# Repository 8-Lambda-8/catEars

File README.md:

# A CatEar headband with LEDs!

[Interactive BOM](https://htmlpreview.github.io/?https://raw.githubusercontent.com/8-Lambda-8/catEars/master/bom/ibom.html)

## Some components are only needed on one of each Pair of ears:
* U1 - ESP01
* U2 - AMS1117-3.3 (3.3V voltage regulator for the ESP)
* C11, C12 - 22uF (Capacitors for voltage regualtor)
* R1, R2, R3 - 10kΩ Resistors (Pull up/donw Resistors for booting the ESP)
* R4 - 120Ω Resistor (signal output from ESP to th WS2812) 

(3D print the CatEars with transparent materials)

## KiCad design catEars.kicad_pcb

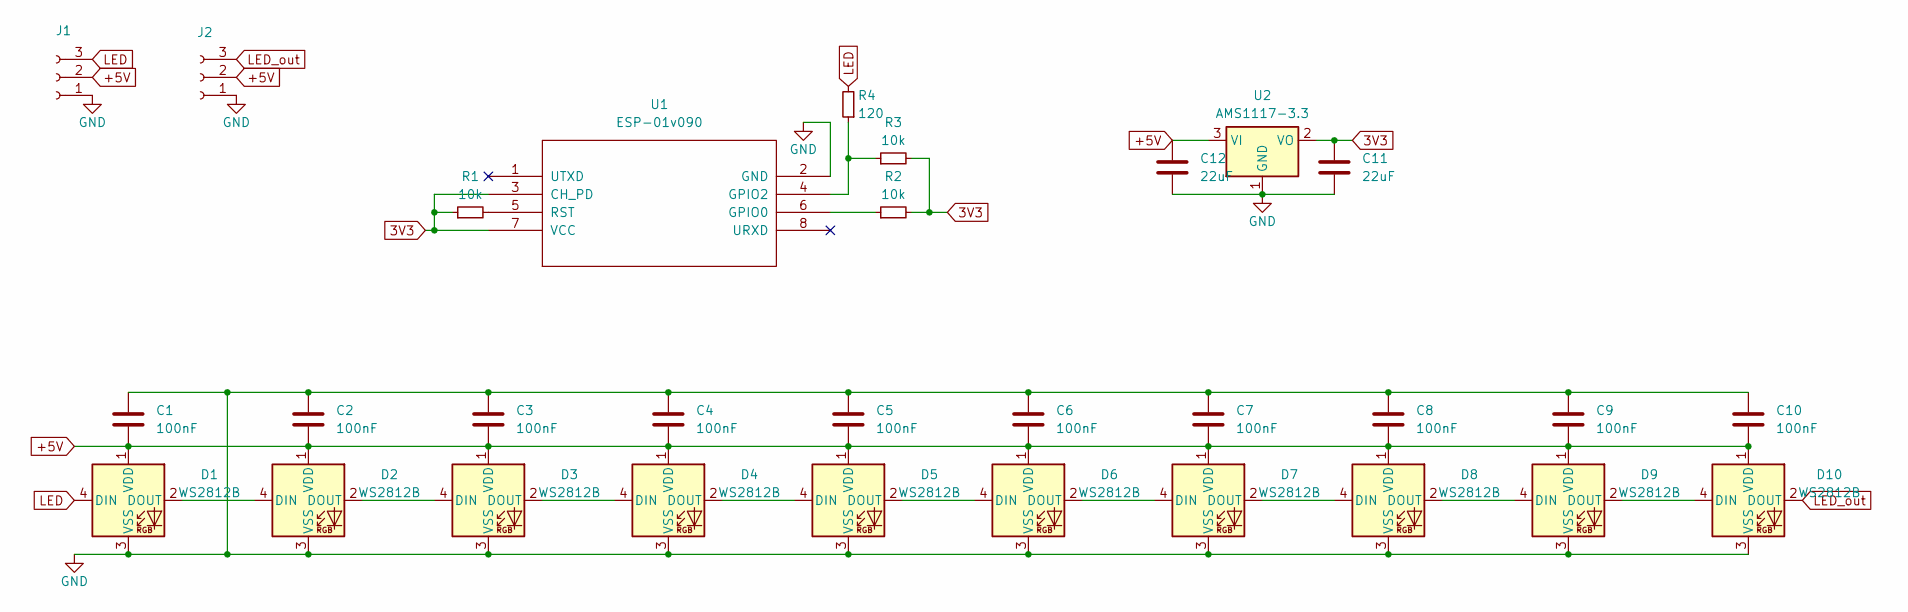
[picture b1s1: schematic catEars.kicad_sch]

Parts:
C1, C2, C3, C4, C5, C6, C7, C8, C9, C10: 100nF; C_0805_2012Metric_Pad1.18x1.45mm_HandSolder
C11, C12: 22uF; C_0805_2012Metric_Pad1.18x1.45mm_HandSolder
D1, D2, D3, D4, D5, D6, D7, D8, D9, D10: WS2812B; LED_WS2812B_PLCC4_5.0x5.0mm_P3.2mm
J1, J2: PinHeader_1x03_P2.54mm_Vertical
R1, R2, R3: 10k; R_0805_2012Metric_Pad1.20x1.40mm_HandSolder
R4: 120; R_0805_2012Metric_Pad1.20x1.40mm_HandSolder
U1: ESP-01v090; ESP-01
U2: AMS1117-3.3; SOT-223-3_TabPin2

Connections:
3V3: C11.1, R1.1, R2.2, R3.2, U1.3 (CH_PD), U1.7 (VCC), U2.2 (VO); also elsewhere on the board
+5V: C1.2, C2.2, C3.2, C4.2, C5.2, C6.2, C7.2, C8.2, C9.2, C10.2, C12.1, D1.1 (VDD), D2.1 (VDD), D3.1 (VDD), D4.1 (VDD), D5.1 (VDD), D6.1 (VDD), D7.1 (VDD), D8.1 (VDD), D9.1 (VDD), D10.1 (VDD), J1.2, J2.2, U2.3 (VI)
GND: C1.1, C2.1, C3.1, C4.1, C5.1, C6.1, C7.1, C8.1, C9.1, C10.1, C11.2, C12.2, D1.3 (VSS), D2.3 (VSS), D3.3 (VSS), D4.3 (VSS), D5.3 (VSS), D6.3 (VSS), D7.3 (VSS), D8.3 (VSS), D9.3 (VSS), D10.3 (VSS), J1.1, J2.1, U1.2 (GND), U2.1 (GND); also elsewhere on the board
LED: D1.4 (DIN), J1.3, R4.2
LED_out: D10.2 (DOUT), J2.3
unnamed: D1.2 (DOUT), D2.4 (DIN)
unnamed: D2.2 (DOUT), D3.4 (DIN)
unnamed: D3.2 (DOUT), D4.4 (DIN)
unnamed: D4.2 (DOUT), D5.4 (DIN)
unnamed: D5.2 (DOUT), D6.4 (DIN)
unnamed: D6.2 (DOUT), D7.4 (DIN)
unnamed: D7.2 (DOUT), D8.4 (DIN)
unnamed: D8.2 (DOUT), D9.4 (DIN)
unnamed: D9.2 (DOUT), D10.4 (DIN)
unnamed 14: R2.1, U1.6 (GPIO0); also elsewhere on the board
unnamed 15: R3.1, R4.1, U1.4 (GPIO2); also elsewhere on the board
unnamed 16: R1.2, U1.5 (RST); also elsewhere on the board

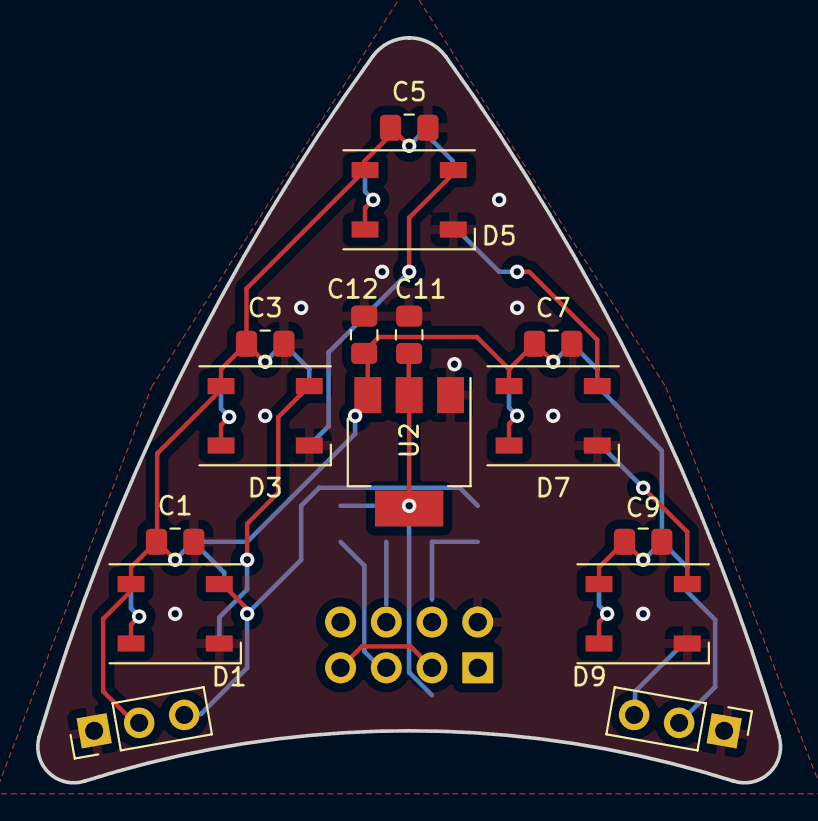
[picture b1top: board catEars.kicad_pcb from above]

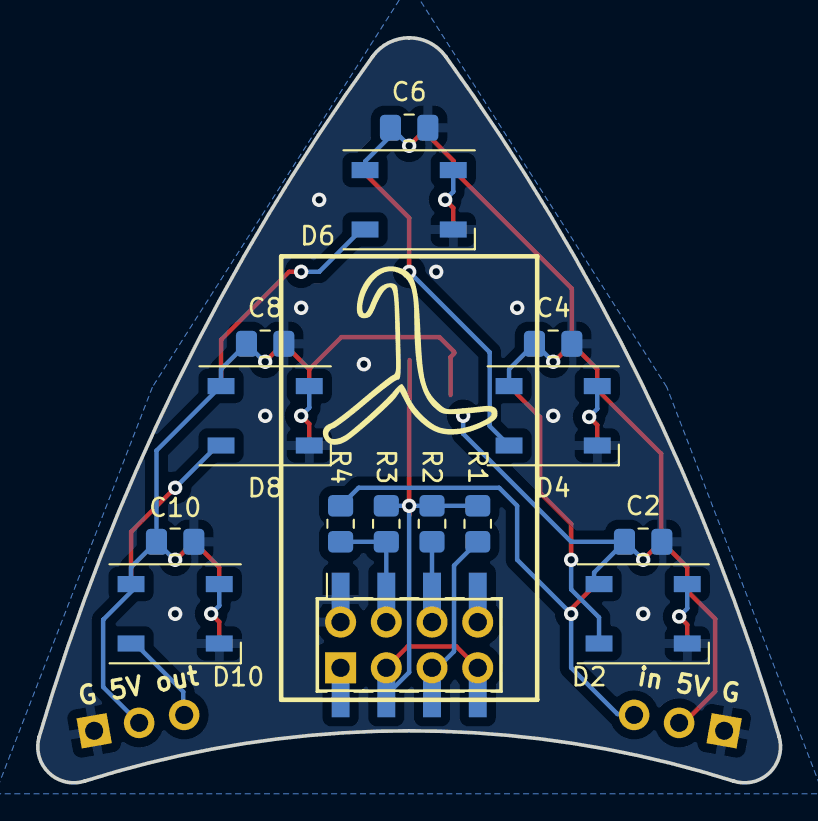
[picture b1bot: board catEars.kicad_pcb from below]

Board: 2 copper layers, 41.3 x 41.4 mm, 31 parts (16 on the bottom side), 17 nets.

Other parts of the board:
U1_: PinSocket_2x04_P2.54mm_Vertical_SMD

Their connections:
3V3: U1_.4, U1_.8; also elsewhere on the board
GND: U1_.1; also elsewhere on the board
unnamed 14: U1_.5; also elsewhere on the board
unnamed 15: U1_.3; also elsewhere on the board
unnamed 16: U1_.6; also elsewhere on the board

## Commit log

2023-12-31 init
2024-01-04 added .gitignore
2024-01-04 fixed WS2812 VSS VDD
2024-01-07 some optimisations
2024-01-07 moved PCB to origin
2024-01-20 added gerber folder to gitignore
2024-01-23 changed led order from left to right
2024-01-23 changed R12 value
2024-01-23 pcb update
2024-01-23 new positioning for components
2024-02-10 added 2 leds in schematic
2024-02-10 added 2 leds and smd ESP Socket to PCB
2024-02-10 updated board outlines
2024-02-11 created pannel
2024-03-20 added ibom
2024-03-20 added 3D Files
2024-03-20 removed KiKit footprints from iBOM
2024-12-23 improved stl file
2024-12-23 updated .3mf printfile
2024-12-23 changed C11 value
2024-12-23 added wled cfg
